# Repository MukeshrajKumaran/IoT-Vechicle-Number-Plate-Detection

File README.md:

# IoT Vehicle Number Plate Recognition — ESP32-CAM

An IoT-based number plate recognition system using the ESP32-CAM module. Captures an image on button press, uploads it to a cloud OCR API over HTTPS, and displays the detected number plate on an OLED screen.

---

## How It Works

```
Button Press
     ↓
ESP32-CAM captures JPEG image
     ↓
Image sent via HTTPS POST to circuitdigest.cloud API
     ↓
API returns detected number plate string
     ↓
Result displayed on SSD1306 OLED
```

---

## Hardware

| Component | Details |
|---|---|
| Microcontroller | ESP32-CAM (AI-Thinker) |
| Display | SSD1306 OLED 128×32 (I2C) |
| Trigger | Push button on GPIO 13 |
| Flash | LED on GPIO 4 |
| I2C SDA | GPIO 15 |
| I2C SCL | GPIO 14 |

> ESP32-CAM does not expose default I2C pins, so SDA/SCL are manually assigned using the `TwoWire` API.

---

## Features

- JPEG image capture using the ESP32 camera driver
- HTTPS POST with multipart/form-data image upload
- JSON response parsing to extract number plate string
- OLED status display for each stage (connecting, uploading, result)
- PSRAM-aware configuration — uses higher resolution and quality when PSRAM is available
- Image sent in 1KB chunks to handle large frame buffers

---

## Setup

### 1. CH340 USB-to-Serial Driver

Required to flash the ESP32-CAM from your PC.
Download: [https://www.wch-ic.com/downloads/CH341SER_EXE.html](https://www.wch-ic.com/downloads/CH341SER_EXE.html)

> If your board uses a CP2102 chip instead, use the Silicon Labs driver:
> [https://www.silabs.com/developers/usb-to-uart-bridge-vcp-drivers](https://www.silabs.com/developers/usb-to-uart-bridge-vcp-drivers)

After installing, the board should appear as a COM port in Device Manager (Windows) or `/dev/ttyUSB0` (Linux/macOS).

### 2. ESP32 Board Support

Add the ESP32 board package to Arduino IDE:

1. Go to **File → Preferences**
2. Add this to Additional Boards Manager URLs:
   ```
   https://raw.githubusercontent.com/espressif/arduino-esp32/gh-pages/package_esp32_index.json
   ```
3. Go to **Tools → Board → Boards Manager**, search `esp32`, install **esp32 by Espressif Systems**
4. Select board: **AI Thinker ESP32-CAM**

### 3. Libraries

Install via **Tools → Manage Libraries**:
- `Adafruit GFX Library`
- `Adafruit SSD1306`

### 4. Configuration

In `main.cpp`, update:

```cpp
const char* ssid = "your_wifi_ssid";
const char* password = "your_wifi_password";
String apiKey = "your_api_key";  // from circuitdigest.cloud
```

### 5. Flash

```
Board       : AI Thinker ESP32-CAM
Port        : COMX
Upload Speed: 115200
```

Connect GPIO 0 to GND before flashing. Remove the jumper and press reset to run.

---

## Project Structure

```
├── main.ino      # Full firmware source
└── README.md
```

---

## Notes

- `client.setInsecure()` skips TLS certificate validation — acceptable for prototyping, not for production
- Flash LED is present but commented out — uncomment the `digitalWrite(flashLight, ...)` lines in `sendPhoto()` to enable
- Server response timeout is 5 seconds — adjust based on API response time

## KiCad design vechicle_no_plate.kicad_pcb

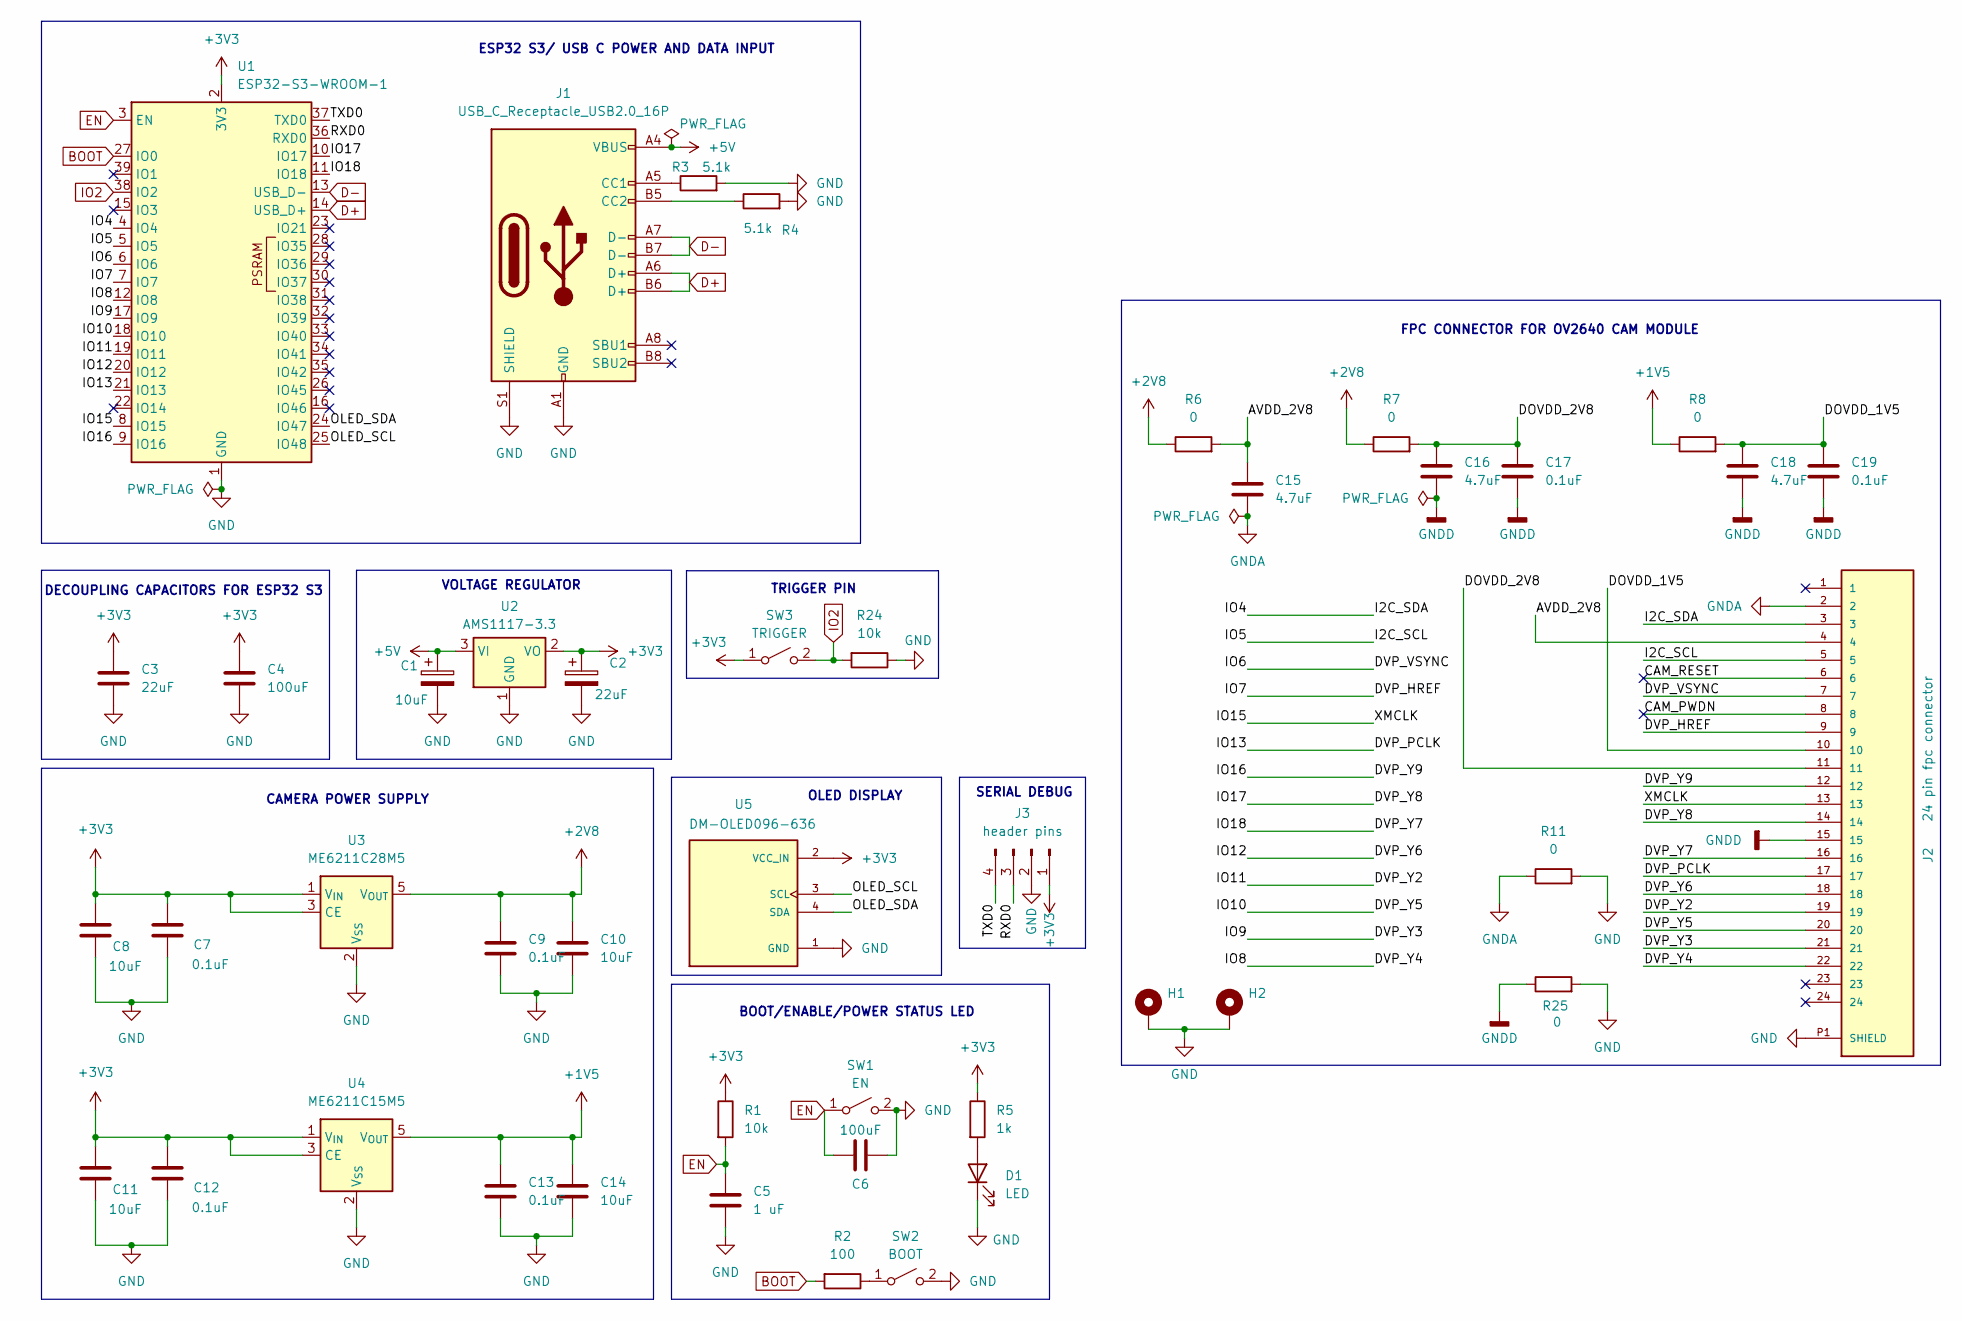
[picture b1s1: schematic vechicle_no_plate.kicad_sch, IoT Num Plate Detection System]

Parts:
C1, C8, C10, C11, C14: 10uF; C_0805_2012Metric
C2, C3: 22uF; C_1206_3216Metric
C4, C6: 100uF; C_1210_3225Metric
C5: 1 uF; C_0201_0603Metric
C7, C9, C12, C13, C17, C19: 0.1uF; C_0201_0603Metric
C15, C16, C18: 4.7uF; C_0805_2012Metric
D1: LED; LED_0201_0603Metric_Pad0.64x0.40mm_HandSolder
H1, H2: MountingHole_Pad; MountingHole_3.2mm_M3_Pad_Via
J1: USB_C_Receptacle_USB2.0_16P; USB_C_Receptacle_GCT_USB4105-xx-A_16P_TopMnt_Horizontal
J2: 24 pin fpc connector; HRS_FH12-24S-0.5SH_55_
J3: header pins; PinHeader_1x04_P1.00mm_Vertical
R1, R24: 10k; R_0201_0603Metric
R2: 100; R_0201_0603Metric
R3, R4: 5.1k; R_0201_0603Metric
R5: 1k; R_0201_0603Metric
R6, R7, R8, R11, R25: 0; R_0201_0603Metric
SW1: EN; SW_SPST_PTS647_Sx38
SW2: BOOT; SW_SPST_PTS647_Sx38
SW3: TRIGGER; SW_SPST_PTS647_Sx38
U1: ESP32-S3-WROOM-1
U2: AMS1117-3.3; SOT-223-3_TabPin2
U3: ME6211C28M5; SOT-23-5
U4: ME6211C15M5; SOT-23-5
U5: DM-OLED096-636; MODULE_DM-OLED096-636; PARTREV 2018-09-10

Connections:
+1V5: C13.1, C14.1, R8.1, U4.5 (V_{OUT})
+2V8: C9.1, C10.1, R6.1, R7.1, U3.5 (V_{OUT})
+3V3: C2.1, C3.1, C4.1, C7.1, C8.1, C11.1, C12.1, J3.1, R1.1, R5.1, SW3.1 (A), U1.2 (3V3), U2.2 (VO), U3.1 (V_{IN}), U3.3 (CE), U4.1 (V_{IN}), U4.3 (CE), U5.2 (VCC_IN)
+5V: C1.1, J1.A4 (VBUS), J1.A9 (VBUS), J1.B4 (VBUS), J1.B9 (VBUS), U2.3 (VI)
/AVDD_2V8: C15.2, J2.4, R6.2
/CAM_PWDN: J2.8
/CAM_RESET: J2.6
/DOVDD_1V5: C18.2, C19.2, J2.10, R8.2
/DOVDD_2V8: C16.2, C17.2, J2.11, R7.2
/DVP_HREF: J2.9, U1.7 (IO7)
/DVP_PCLK: J2.17, U1.21 (IO13)
/DVP_VSYNC: J2.7, U1.6 (IO6)
/DVP_Y2: J2.19, U1.19 (IO11)
/DVP_Y3: J2.21, U1.17 (IO9)
/DVP_Y4: J2.22, U1.12 (IO8)
/DVP_Y5: J2.20, U1.18 (IO10)
/DVP_Y6: J2.18, U1.20 (IO12)
/DVP_Y7: J2.16, U1.11 (IO18)
/DVP_Y8: J2.14, U1.10 (IO17)
/DVP_Y9: J2.12, U1.9 (IO16)
/I2C_SCL: J2.5, U1.5 (IO5)
/I2C_SDA: J2.3, U1.4 (IO4)
/IO15: J2.13, U1.8 (IO15)
/OLED_SCL: U1.25 (IO48), U5.3 (SCL)
/OLED_SDA: U1.24 (IO47), U5.4 (SDA)
/RXD0: J3.3, U1.36 (RXD0)
/TXD0: J3.4, U1.37 (TXD0)
BOOT: R2.2, U1.27 (IO0)
D+: J1.A6 (D+), J1.B6 (D+), U1.14 (USB_D+)
D-: J1.A7 (D-), J1.B7 (D-), U1.13 (USB_D-)
EN: C5.1, C6.2, R1.2, SW1.1 (A), U1.3 (EN)
GND: C1.2, C2.2, C3.2, C4.2, C5.2, C6.1, C7.2, C8.2, C9.2, C10.2, C11.2, C12.2, C13.2, C14.2, D1.1 (K), H1.1, H2.1, J1.A1 (GND), J1.A12 (GND), J1.B1 (GND), J1.B12 (GND), J1.S1 (SHIELD), J2.P1 (SHIELD), J2.P2 (SHIELD), J3.2, R3.2, R4.2, R11.2, R24.1, R25.2, SW1.2 (B), SW2.2 (B), U1.1 (GND), U1.40 (GND), U1.41 (GND), U2.1 (GND), U3.2 (V_{SS}), U4.2 (V_{SS}), U5.1 (GND)
GNDA: C15.1, J2.2, R11.1
GNDD: C16.1, C17.1, C18.1, C19.1, J2.15, R25.1
IO2: R24.2, SW3.2 (B), U1.38 (IO2)
unnamed: D1.2 (A), R5.2
unnamed: J1.A5 (CC1), R3.1
unnamed: J1.B5 (CC2), R4.1
unnamed: R2.1, SW2.1 (A)

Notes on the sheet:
VOLTAGE REGULATOR
TRIGGER PIN
FPC CONNECTOR FOR OV2640 CAM MODULE
SERIAL DEBUG
BOOT/ENABLE/POWER STATUS LED
OLED DISPLAY
CAMERA POWER SUPPLY
DECOUPLING CAPACITORS FOR ESP32 S3
ESP32 S3/ USB C POWER AND DATA INPUT

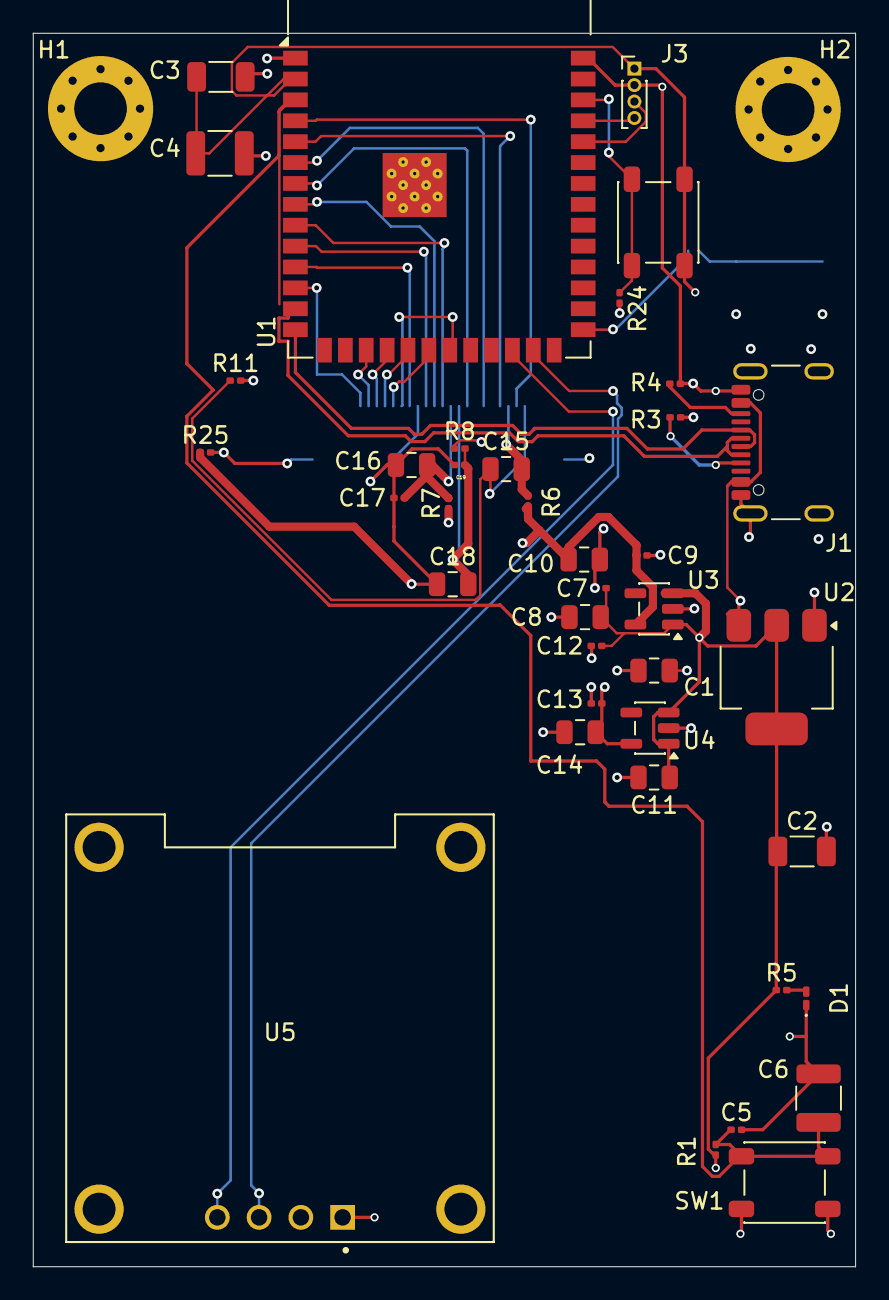
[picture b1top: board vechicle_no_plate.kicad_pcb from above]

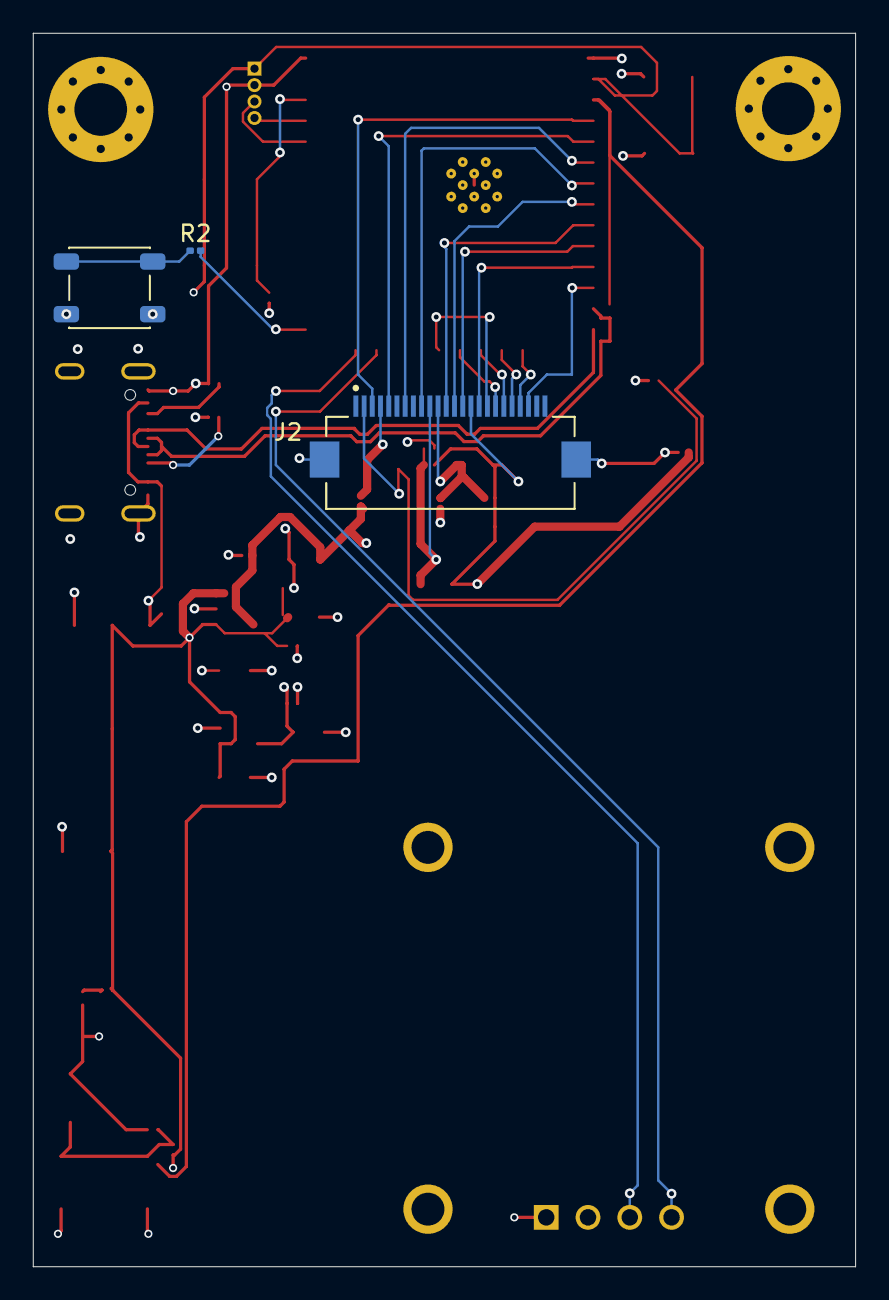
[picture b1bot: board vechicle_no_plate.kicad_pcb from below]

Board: 4 copper layers, 50.0 x 75.0 mm, 44 parts (3 on the bottom side), 37 nets.

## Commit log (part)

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2026-06-13 Rename IOT.ino to main.ino
